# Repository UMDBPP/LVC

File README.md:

# LVC
Low Voltage Cutoff Hardware for LiPo Battery Protection

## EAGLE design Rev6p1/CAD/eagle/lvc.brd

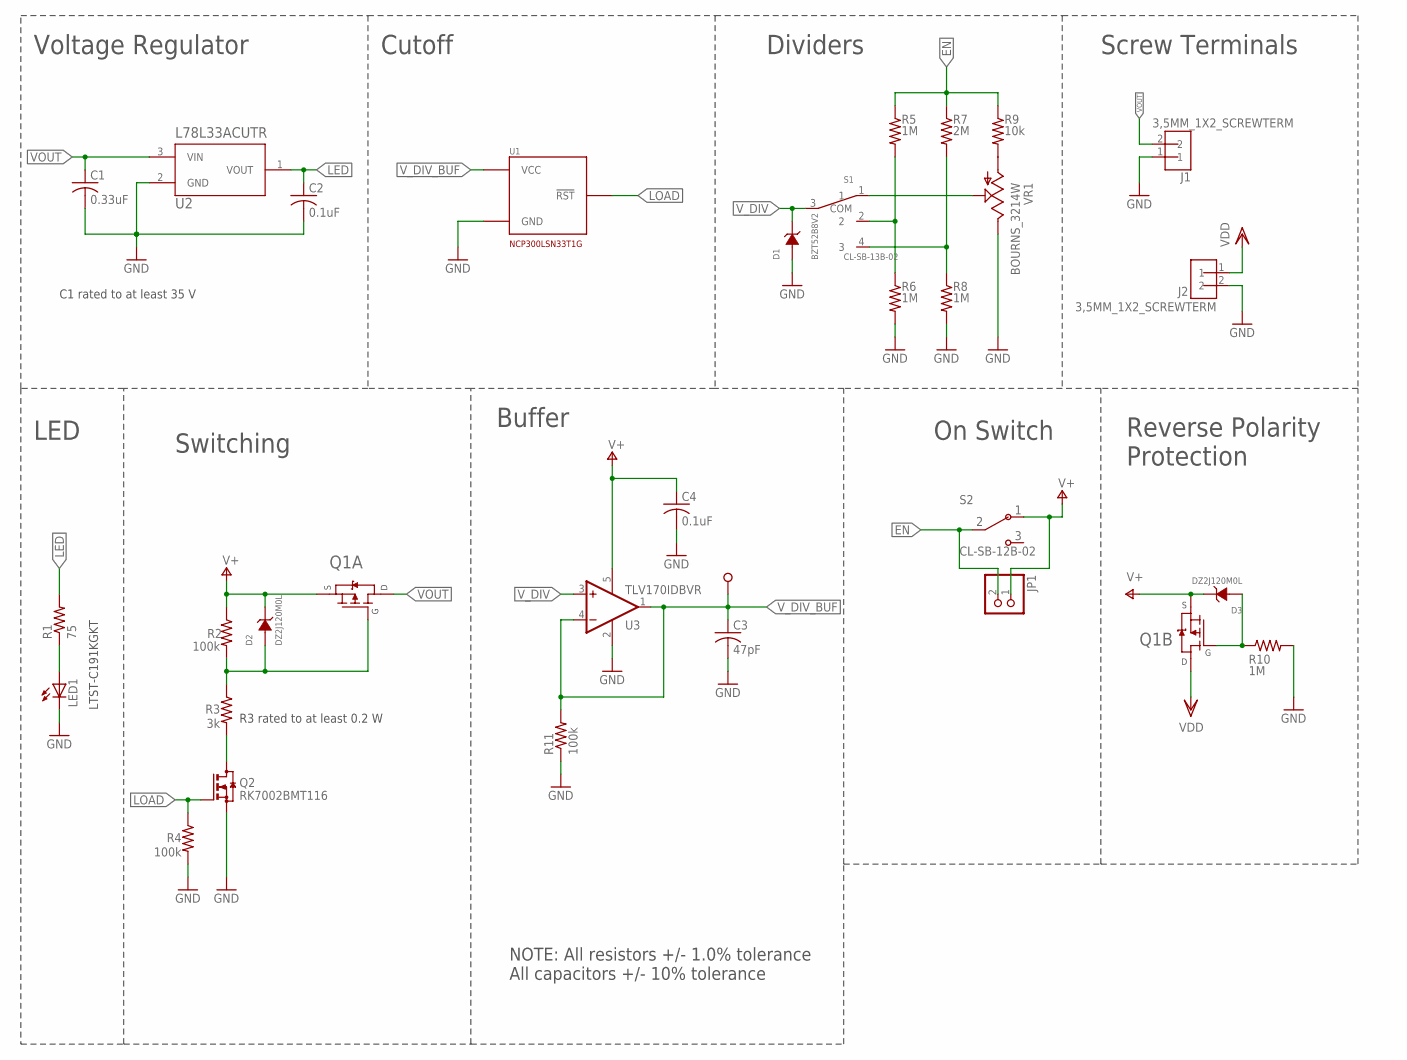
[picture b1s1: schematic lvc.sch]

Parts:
C1: 0.33uF; C0603
C2, C4: 0.1uF; C0603
C3: 47pF; C0603
D1: BZT52B8V2; SOD123
D2, D3: DZ2J120M0L; SMINI2-F5-B
J1, J2: 3,5MM_1X2_SCREWTERM; 3.5MM_1X2
JP1: PINHD-1X2; 1X02
LED1: LEDCHIPLED_0603; CHIPLED_0603
Q1: SI7997DP; POWERPAK-SO-8-DUAL
Q2: RK7002BMT116; SOT23
R1: 75; R0603
R2, R4, R11: 100k; R0603
R3: 3k; R0603
R5, R6, R8, R10: 1M; R0603
R7: 2M; R0603
R9: 10k; R0603
S1: CL-SB-13B-02; CL-SB-13B
S2: CL-SB-12B-02; CL-SB-12B
TP2: TESTPOINTNOCREAM; TP_2.5MM_NOCREAM
U1: NCP300LSN33T1G; SOT23-5
U2: L78L33ACUTR; SOT-89
U3: TLV170IDBVR; SOT23-DBV
VR1: BOURNS_3214W; J-LEAD_TOP_ADJ

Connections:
2_CELL: R5.2, R6.1, S1.2
3_CELL: R7.2, R8.1, S1.4 (3)
EN: JP1.2, R5.1, R7.1, R9.1, S2.1
GND: C1.2, C2.2, C3.2, C4.2, D1.A, J1.1, J2.2, LED1.C, Q2.2 (S), R4.2, R6.2, R8.2, R10.2, R11.1, U1.3 (GND), U2.2 (GND), U3.2 (V-), VR1.3 (E)
LED: C2.1, R1.2, U2.1 (VOUT)
LOAD: Q2.1 (G), R4.1, U1.1 (!RST!)
unnamed: LED1.A, R1.1
unnamed: D2.A, Q1.4 (G), R2.2, R3.1
unnamed: D3.A, Q1.2 (G), R10.1
unnamed: Q2.3 (D), R3.2
unnamed: S1.1, VR1.2 (S)
unnamed: R9.2, VR1.1 (A)
V+: C4.1, D2.C, D3.C, JP1.1, Q1.1 (S), Q1.3 (S), R2.1, S2.2, U3.5 (V+)
VDD: J2.1, Q1.7 (D), Q1.8 (D), Q1.8L (D)
VOUT: C1.1, J1.2, Q1.5 (D), Q1.5L (D), Q1.6 (D), U2.3 (VIN)
V_DIV: D1.C, S1.3 (COM), U3.3 (+IN)
V_DIV_BUF: C3.1, R11.2, TP2.P$1, U1.2 (VCC), U3.1 (OUT), U3.4 (-IN)

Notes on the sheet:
Voltage Regulator
LED
Switching
Dividers
Screw Terminals
On Switch
Reverse Polarity Protection
Cutoff
LTST-C191KGKT
NOTE: All resistors +/- 1.0% tolerance All capacitors +/- 10% tolerance
C1 rated to at least 35 V
R3 rated to at least 0.2 W
Buffer

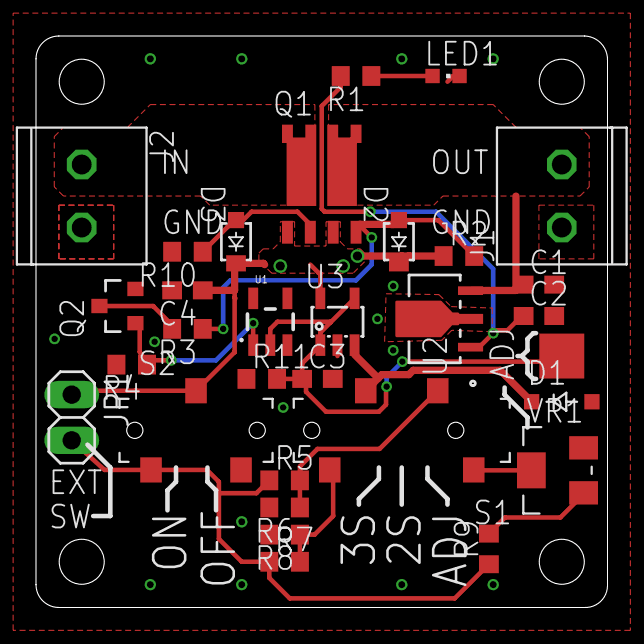
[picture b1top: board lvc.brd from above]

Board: 2 copper layers, 31.8 x 31.8 mm, 31 parts (0 on the bottom side), 17 nets.

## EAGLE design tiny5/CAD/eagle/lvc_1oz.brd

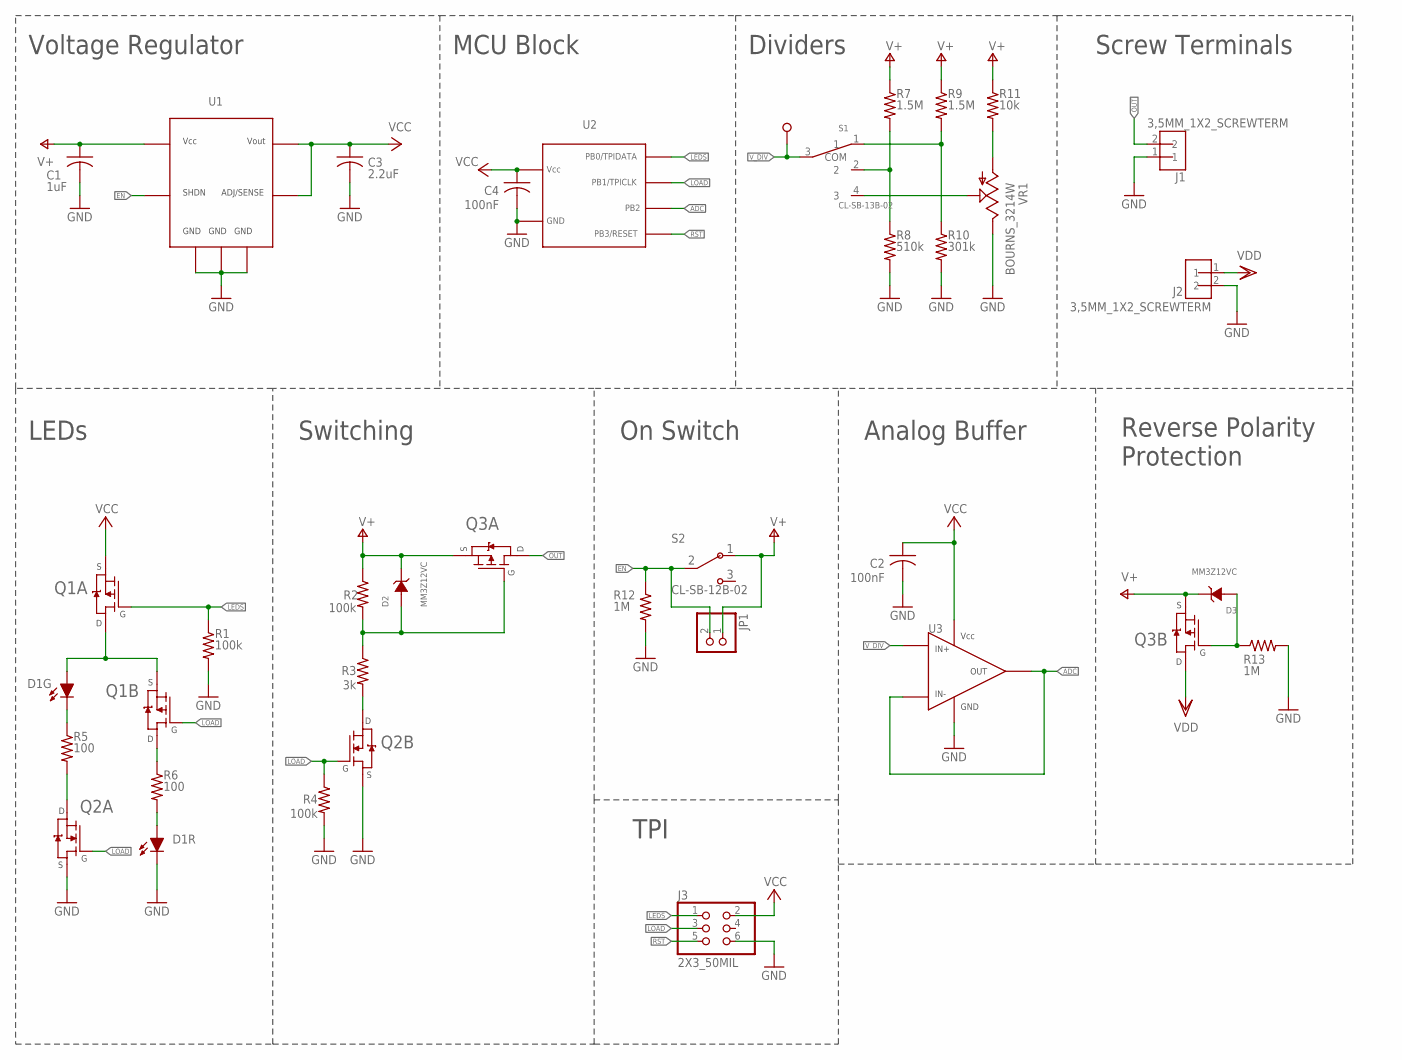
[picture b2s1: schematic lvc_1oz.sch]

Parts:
C1: 1uF; C0603
C2, C4: 100nF; C0603
C3: 2.2uF; C0603
D1: LED-R/G_150141RV73100; 4-PLCC
D2, D3: MM3Z12VC; SOD-323F
J1, J2: 3,5MM_1X2_SCREWTERM; 3.5MM_1X2
J3: 2X3_50MIL; 50MIL_2X3
JP1: PINHD-1X2; 1X02
Q1: FDC6312P; SOT23-6
Q2: PMGD280UN; 6-TSSOP
Q3: SI7997DP; POWERPAK-SO-8-DUAL
R1, R2, R4: 100k; R0603
R3: 3k; R0603
R5, R6: 100; R0603
R7, R9: 1.5M; R0603
R8: 510k; R0603
R10: 301k; R0603
R11: 10k; R0603
R12, R13: 1M; R0603
S1: CL-SB-13B-02; CL-SB-13B
S2: CL-SB-12B-02; CL-SB-12B
TP1: TESTPOINT; TP_2.5MM
U1: LT3007; SOT23-8
U2: ATTINY5; SOT23-6
U3: LT1494; 8-MSOP
VR1: BOURNS_3214W; J-LEAD_TOP_ADJ

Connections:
2_CELL: R7.2, R8.1, S1.2
3_CELL: R9.2, R10.1, S1.1
ADC: U2.4 (PB2), U3.P$2 (IN-), U3.P$6 (OUT)
ADJ: S1.4 (3), VR1.2 (S)
EN: JP1.2, R12.1, S2.1, U1.1 (SHDN)
GND: C1.2, C2.2, C3.2, C4.2, D1.3 (C), J1.1, J2.2, J3.6, Q2.P$1 (S), Q2.P$4 (S), R1.2, R4.2, R8.2, R10.2, R12.2, R13.2, U1.2 (GND1), U1.3 (GND2), U1.4 (GND3), U2.2 (GND), U3.P$4 (GND), VR1.3 (E)
LEDS: J3.1, Q1.1 (G), R1.1, U2.1 (PB0/TPID)
LOAD: J3.3, Q1.3 (G), Q2.P$2 (G), Q2.P$5 (G), R4.1, U2.3 (PB1/TPICLK)
unnamed: D1.4 (C), R5.1
unnamed: Q2.P$6 (D), R5.2
unnamed: D1.2 (A), Q1.2 (S), Q1.6 (D)
unnamed: Q1.4 (D), R6.1
unnamed: D2.1 (A), Q3.4 (G), R2.2, R3.1
unnamed: D3.1 (A), Q3.2 (G), R13.1
unnamed: Q2.P$3 (D), R3.2
unnamed: R11.2, VR1.1 (A)
OUT: J1.2, Q3.5 (D), Q3.5L (D), Q3.6 (D)
RA: D1.1 (A), R6.2
RST: J3.5, U2.6 (PB3/RST)
V+: C1.1, D2.2 (C), D3.2 (C), JP1.1, Q3.1 (S), Q3.3 (S), R2.1, R7.1, R9.1, R11.1, S2.2, U1.5 (VCC)
VCC: C2.1, C3.1, C4.1, J3.2, Q1.5 (S), U1.7 (OUT), U1.8 (ADJ/SENSE), U2.5 (VCC), U3.P$7 (VCC)
VDD: J2.1, Q3.7 (D), Q3.8 (D), Q3.8L (D)
V_DIV: S1.3 (COM), TP1.P$1, U3.P$3 (IN+)

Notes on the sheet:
Voltage Regulator
MCU Block
LEDs
Switching
Dividers
Screw Terminals
Analog Buffer
TPI
On Switch
Reverse Polarity Protection

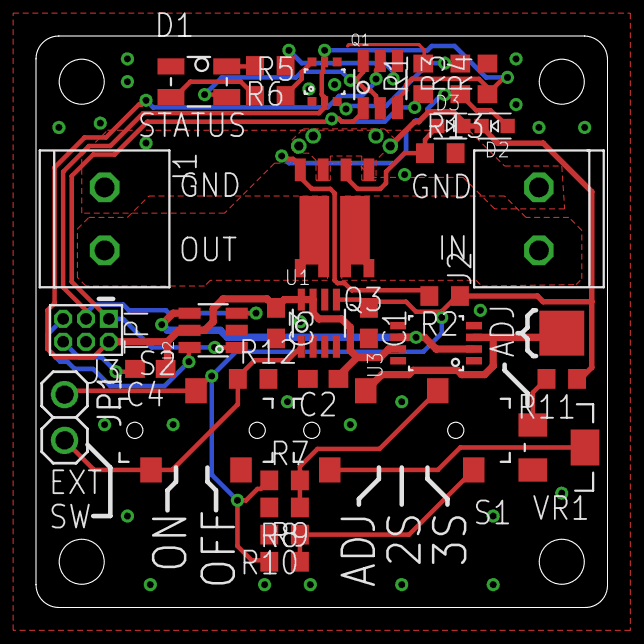
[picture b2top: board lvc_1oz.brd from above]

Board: 2 copper layers, 31.8 x 31.8 mm, 34 parts (0 on the bottom side), 23 nets.

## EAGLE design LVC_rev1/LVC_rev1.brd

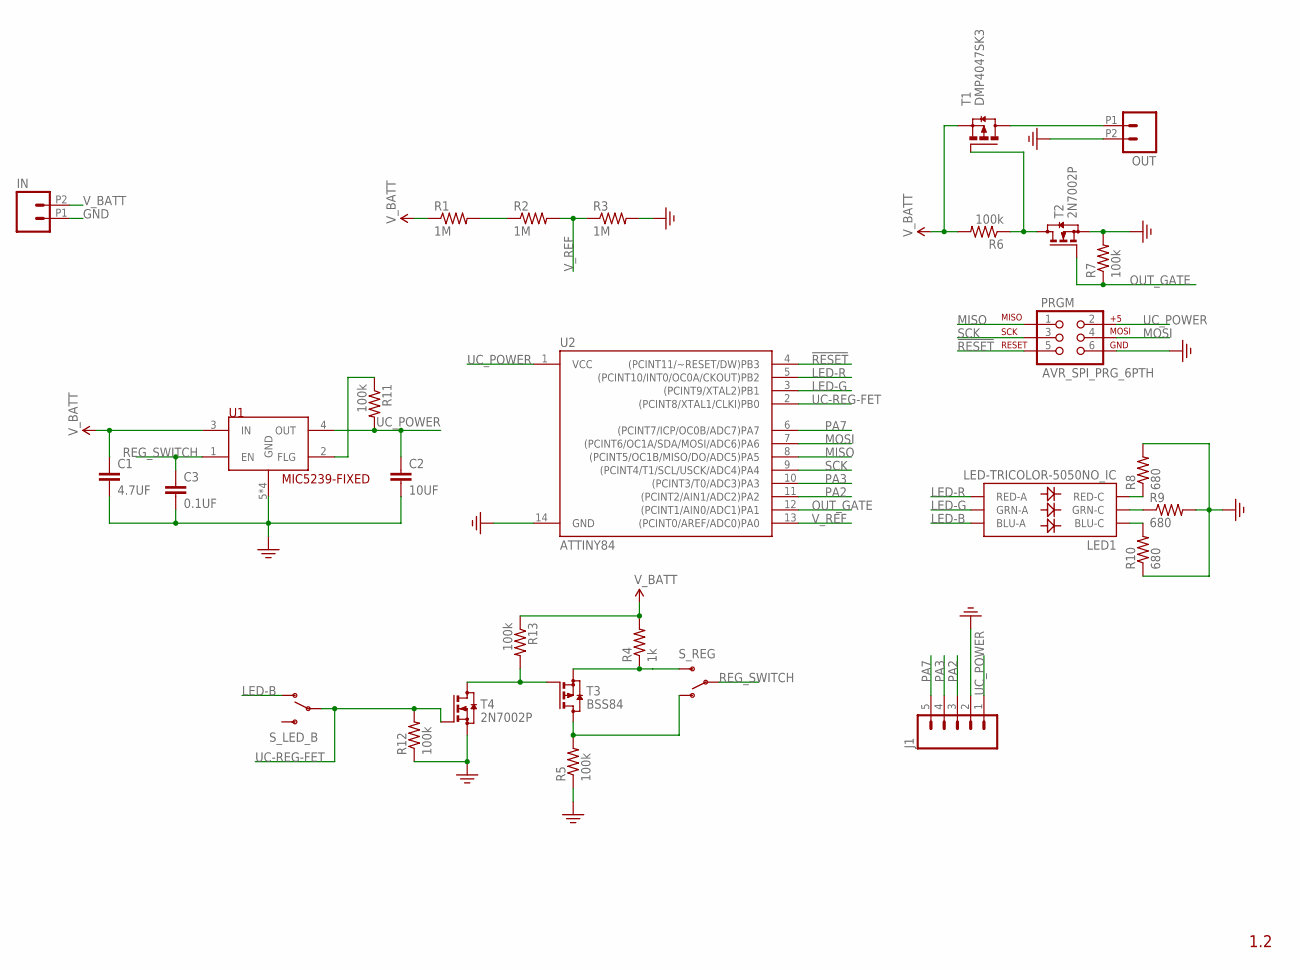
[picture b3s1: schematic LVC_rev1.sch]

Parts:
C1: 4.7UF; C1206
C2: 10UF; C0805
C3: 0.1UF; C0603
IN: M022.54MM_SCREWTERM; 1X02_2.54_SCREWTERM
J1: M05PTH; 1X05
LED1: LED-TRICOLOR-5050NO_IC; LED-TRICOLOR-5050
OUT: M022.54MM_SCREWTERM; 1X02_2.54_SCREWTERM
PRGM: AVR_SPI_PRG_6PTH; 2X3
R1, R2, R3: 1M; R0603
R4: 1k; R0603
R5, R6, R7, R11, R12, R13: 100k; R0603
R8, R9, R10: 680; R0603
S_LED_B: SWITCH-SPDTPTH; SWITCH-SPDT
S_REG: SWITCH-SPDTPTH; SWITCH-SPDT
T1: DMP4047SK3; TO252
T2, T4: 2N7002P; SOT23
T3: BSS84; SOT23
U1: MIC5239-FIXED; SOIC8
U2: ATTINY84; SO14

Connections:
!RESET: PRGM.5, U2.4 ((PCINT11/~RESET/DW)PB3)
BATT_OUT: OUT.P1 (1), T1.3 (D)
GND: C1.2, C2.2, C3.2, IN.P1 (1), J1.2, OUT.P2 (2), PRGM.6, R3.2, R5.1, R7.2, R8.2, R9.2, R10.1, R12.1, T2.2 (S), T4.2 (S), U1.5 (GND), U1.6 (GND), U1.7 (GND), U1.8 (GND), U2.14 (GND)
LED-B: LED1.3 (BLU-A), S_LED_B.1 (O)
LED-G: LED1.1 (GRN-A), U2.3 ((PCINT9/XTAL2)PB1)
LED-R: LED1.2 (RED-A), U2.5 ((PCINT10/INT0/OC0A/CKOUT)PB2)
MISO: PRGM.1, U2.8 ((PCINT5/OC1B/MISO/DO/ADC5)PA5)
MOSI: PRGM.4, U2.7 ((PCINT6/OC1A/SDA/MOSI/ADC6)PA6)
unnamed: LED1.6 (GRN-C), R9.1
unnamed: R4.1, S_REG.3 (S), T3.2 (S)
unnamed: R1.2, R2.1
unnamed: R5.2, S_REG.1 (O), T3.3 (D)
unnamed: R6.1, T1.1 (G), T2.3 (D)
unnamed: LED1.5 (RED-C), R8.1
unnamed: R11.1, U1.2 (FLG)
unnamed: LED1.4 (BLU-C), R10.2
unnamed: R13.2, T3.1 (G), T4.3 (D)
OUT_GATE: R7.1, T2.1 (G), U2.12 ((PCINT1/AIN0/ADC1)PA1)
PA2: J1.3, U2.11 ((PCINT2/AIN1/ADC2)PA2)
PA3: J1.4, U2.10 ((PCINT3/T0/ADC3)PA3)
PA7: J1.5, U2.6 ((PCINT7/ICP/OC0B/ADC7)PA7)
REG_SWITCH: C3.1, S_REG.2, U1.1 (EN)
SCK: PRGM.3, U2.9 ((PCINT4/T1/SCL/USCK/ADC4)PA4)
UC-REG-FET: R12.2, S_LED_B.2, T4.1 (G), U2.2 ((PCINT8/XTAL1/CLKI)PB0)
UC_POWER: C2.1, J1.1, PRGM.2, R11.2, U1.4 (OUT), U2.1 (VCC)
V_BATT: C1.1, IN.P2 (2), R1.1, R4.2, R6.2, R13.1, T1.2 (S), U1.3 (IN)
V_REF: R2.2, R3.1, U2.13 ((PCINT0/AREF/ADC0)PA0)

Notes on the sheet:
1.2

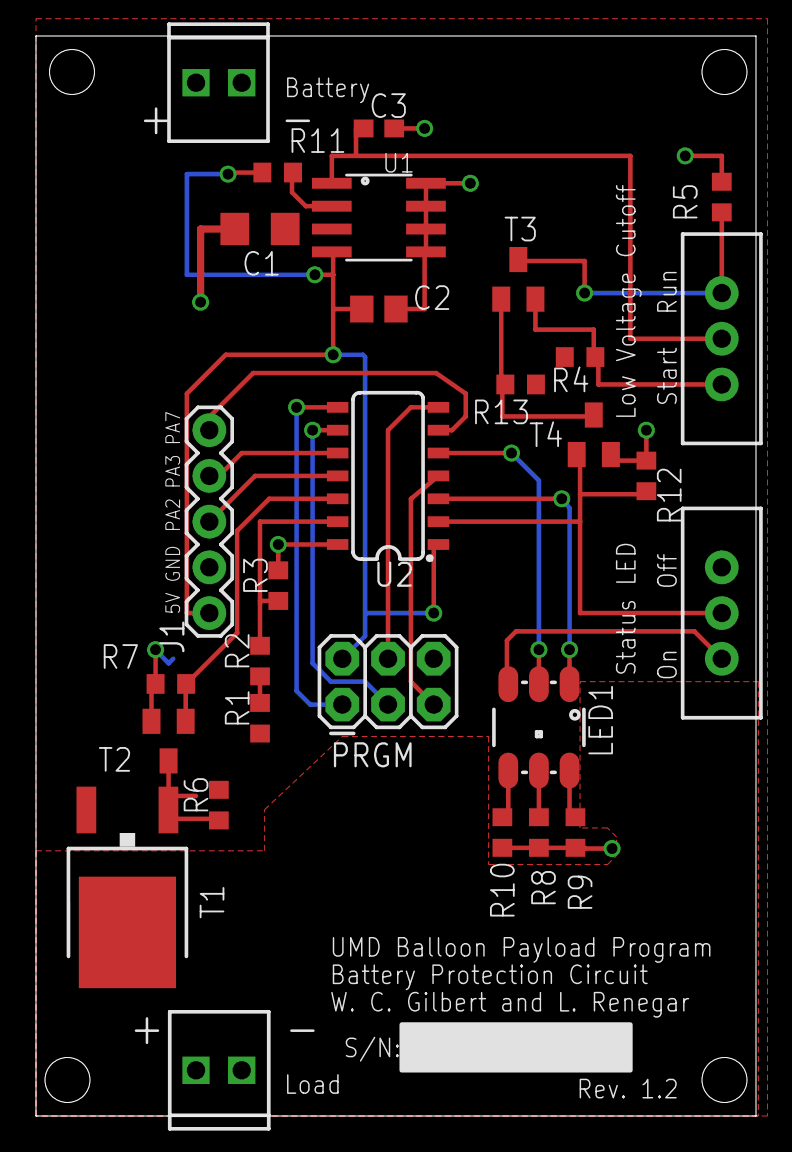
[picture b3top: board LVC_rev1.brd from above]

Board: 2 copper layers, 40.0 x 60.0 mm, 29 parts (0 on the bottom side), 27 nets.

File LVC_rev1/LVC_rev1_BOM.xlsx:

UMD BPP Low Voltage Cutoff Rev 1.2 BOM
Item # | Ref Des | Qty | Manufacturer | Mfg Part # | Description | Package | Type | Dist. 1 | Dist. 1 Part No. | Dist. 2 | Dist. 2 Part No.
1 | C1 | 1 | Samsung EMA | CL31B475KBHNNNE | CAP CER 4.7UF 50V X7R 1206 | 1206 | SMD | Digi-Key | 1276-2789-1-ND
2 | C2 | 1 | Samsung EMA | CL21A106KOQNNNE | CAP CER 10UF 16V X5R 0805 | 0805 | SMD | Digi-Key | 1276-1096-1-ND
3 | C3 | 1 | Murata | GRM188R71E104KA01D | 0.10µF ±10% 25V X7R Ceramic Capacitor | 0603 | SMD | Digi-Key | 490-1524-1-ND
4 | LED1 | 1 | YETDA | 5060BRG4 | LED RGB Common Cathode |  | SMD | Sparkfun | COM-10866
5 | R1, 2, 3 | 3 |  |  | 1M, 0.1% | 0603 | SMD | Digi-Key | A102234CT-ND
6 | R4 | 1 |  |  | 1k, 5% | 0603 | SMD | Digi-Key | 311-1.0KGRCT-ND
7 | R5, 6, 7, 11, 12, 13 | 6 |  |  | 100k, 5% | 0603 | SMD | Digi-Key | 311-100KGRCT-ND
8 | R8, 9, 10 | 3 |  |  | 680, 5% | 0603 | SMD | Digi-Key | 1276-5058-1-ND
9 | U1 | 1 | Micrel | MIC5239-5.0YM | IC REG LDO 5V 0.5A 8SOIC | 8-SOIC | SMD | Digi-Key | 576-1838-5-ND
10 | U2 | 1 | Atmel | ATTINY84-20SSU | IC MCU 8BIT 8KB FLASH 14SOIC | 14-SOIC | SMD | Digi-Key | ATTINY84-20SSU-ND
11 | T1 | 1 | Diodes Incorporated | DMP4047SK3-13 | MOSFET P-CH 40V 20A TO252 | TO-252 | SMD | Digi-Key | DMP4047SK3-13DICT-ND
12 | T2, 4 | 2 | NXP | 2N7002P,215 | MOSFET N-CH 60V 0.36A SOT-23 | SOT23-3 | SMD | Digi-Key | 568-5818-1-ND
13 | T3 | 1 | Infineon | BSS84PH6327XTSA2 | MOSFET P-CH 60V 170MA SOT-23 | SOT23 | SMD | Digi-Key | BSS84PH6327XTSA2CT-ND
14 | S1, 2 | 2 | Sparkfun |  | SPDT Slide Switch |  | Thru-Hole | Sparkfun | COM-09609
15 | PRGM | 1 | Sparkfun | PRT-12807 | 6 Pin programming header |  | Thru-Hole | Sparkfun | PRT-12807
16 | J1 |  |  |  | 5 pin linear header 0.1" spacing |  |  |  | Do not populate
17
18
19
20
21
22

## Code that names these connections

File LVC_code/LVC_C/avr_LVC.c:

// Low Voltage Cutoff Code
// Written by: William Cooper Gilbert on 11 November, 2015
// Revised by: Aravind Ramakrishnan on 23 May, 2016
// Revised by: William Cooper Gilbert on 24 May, 2016
// Rewritten by: Aravind Ramakrishnan on 26 June, 2016 (from Arduino to AVR C)
// Thanks given to Nick Rossomando for guidance

/*
PURPOSE
The purpose of this program is to prevent permanent damage of lithium polymer (LiPo) flight batteries due to deep discharge, where the battery is depleted beyond 80% of its
stated capacity, as indicated by the voltage dropping below 3.25v per cell. This is achieved by using MOSFETs as swtiches, with the gates controlled by an AT-Tiny 84 micro-
controller. When the flight battery in question is above the designated 3.25v per cell voltage, as read by the microcontroller, the gates are set to allow current to flow
to the load, and a green LED is used to show that the battery is above the threshold. When the battery voltage drops below 3.25v per cell, the gates are set to turn off the
current to the load, a red LED is turned on to indicate this visually, and a countdown begun, for ~1.5 hours. If the battery dropped below 3.25v per cell for only a brief time,
the system will turn back on, current will flow to the load, and the green LED will be reactivated. However, it the battery is genuinely depleted, and remains depleted for ~1.5 hours,
the microcontroller will turn off the enable pin that allows the voltage regulator powering the microcontroller to operate, shutting the entire system down except for the
quiescent current flowing through the regulator. This state is called ultra low power mode. A blue LED is used to indicate the status of the enable pin on the regulator: the blue 
LED being on indicates that the regulator is enabled, while the blue LED being off indicates that the regulator is not enabled. A toggle switch on the board allows the blue LED
to be disconnected to save power during flight.

HARDWARE
Surface-mount Device (SMD) Low Voltage Cutoff (LVC) Circuit Board using AT-Tiny 84 microcontroller

OPERATION
Set switches to RUN and LED ON, and connect battery, observe all LEDs are off
Set switch to START, observe blue and green LEDs on simultaneously
Set switch to LED OFF, observe only green LED on
Set switch to RUN, observe only the green LED on
 */

/* Includes */
#include <avr/io.h>
#include <util/delay.h>

/* Pin Definitions */
#define VOLTAGE_DIV PA0 // pin for the voltage divider, used to read the value of the battery. Use in analog mode.
#define LOAD PA1 // pin for Load MOSFETs, used to allow current to flow to the load
#define ENABLE PB0 // digital pin for Enable MOSFETs, used to enable voltage regulator operation
#define GREEN_LED PB1 // digital pin for the Green LED, meaning the battery is charged
#define RED_LED PB2 // digital pin for the Red LED, meaning the battery is depleted

/* Behavioral Constants */
#define LOAD_THRESHOLD 663 // battery threshold with load. 663/1023*5*3: 9.72 volts. *5 becuase this is a 5V microcontroller, *3 becuase this is a 3-cell LiPo (~3.25v per cell threshold). *** From testing, actual cutoff appears to be 9.67V.
#define NO_LOAD_THRESHOLD 700 // battery threshold with no load. 700/1023*5*3: 10.26 volts (Arbitrary, but at least 0.5v greater than Load Threshold voltage). *** From testing, actual value appears to be 10.50V.
#define WAIT_TIME 5000 // time after battery voltage drops below threshold with load before the enable pin is turned off, putting the system into ultra low power mode

/* Function Prototypes */
void init_ADC(); // for setting up the analog conversion on the voltage divider pin
int read_ADC(); // read the voltage divider pin
void work(); // normal execution
void halt(char *battery_status); // battery is now depleted, so turn load off, set LED output
void wait(int *time); // while battery is depleted, increment timer to check for timeout and wait
void resurrect(char *battery_status, int *time); // if battery depletion reading was in error, continue executing normally
void kill(); // after timeout, put into ultra low power mode

int main() {
	/* Program Variables */
	int voltage; // value of current voltage.
	char battery_status = 'a'; // Battery on/off. On = 'a', OFF = 'd'.
	int time = 0; // variable to keep track of runtime after battery drops below threshold.

	/* Enable Pins */
	DDRA |= (1 << LOAD);
	DDRB |= (1 << ENABLE);
	DDRB |= (1 << GREEN_LED);
	DDRB |= (1 << RED_LED);
	init_ADC();

	/* Execution Block */
	while (1) {
		voltage = read_ADC();
		if (battery_status == 'a') { // if battery is ON
			PORTB |= (1 << ENABLE); // set system to "run", the mode used during flight
			if (voltage > LOAD_THRESHOLD) { // if battery is charged
				work();
			}
			else { // if battery is depleted
				halt(&battery_status);
			}
		}
		else {
			if (time < WAIT_TIME) { // if inactivity countdown has not yet expired
				if (voltage < NO_LOAD_THRESHOLD) { // if battery remains depleted
					wait(&time);
				}
				else { // if battery depletion reading was in error
					resurrect(&battery_status, &time);
				}
			}
			else { // if inactivity countdown has expired
				kill();
			}
		}
	}
	return 0; // should never be reached
}

void init_ADC() {
	ADCSRA |= (1 << ADPS2) | (1 << ADPS1) | (0 << ADPS0); // set prescalar to 16
	// ADMUX is fine as it is - PA0 is set with 5:0 set to 0, and to use Vcc, REFS{0,1} should be 0
	DIDR0 |= (1 << ADC0D); // disable digital input
	// For ATTiny84, there is no free running mode
	ADCSRA |= (1 << ADEN); // enable analog digital conversion
}

int read_ADC() {
	ADCSRA |= (1 << ADSC); // start analog digital conversion
	while (ADCSRA & (1 << ADSC)); // wait for read to finish
	return ADC; // return analog value: Vin * 1024 / Vref. (Vref is 5V)
}

void work() {
	PORTA |= (1 << LOAD); // turn load ON
	PORTB |= (1 << GREEN_LED); // turn green LED ON
	PORTB &= ~(1 << RED_LED); // turn red LED OFF
}

void halt(char *battery_status) {
	PORTA &= ~(1 << LOAD); // turn the load OFF
	PORTB &= ~(1 << GREEN_LED); // turn the green LED OFF
	PORTB |= (1 << RED_LED); // turn the red LED ON
	*battery_status = 'd'; // turn battery off
	_delay_ms(3000); // wait three seconds for transients to settle
}

void wait(int *time) {
	(*time)++; // increment inactivity countdown
	_delay_ms(1000); // inactivity countdown is by seconds
}

void resurrect(char *battery_status, int *time) {
	*battery_status = 'a';
	*time = 0;
	_delay_ms(3000); // wait three seconds for transients to settle
}

void kill() {
	PORTB &= ~(1 << ENABLE); // put the battery into ultra low power mode
}

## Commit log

2016-05-21 Rev 1.2 - added C3 to fix start/run switch
2016-05-21 Updated BOM for rev 1.2
2016-05-22 Fixed via error
2016-05-22 Added .gitignore
2016-05-22 Changed documentation error with T2
2016-05-22 Removed extraneous files
2016-05-22 Updated gitignore
2016-05-22 Removed eagle preferences file from git repository (contains data about local machine, not project)
2016-05-27 uploaded the current code for the LVC
2016-05-27 removed vim swap file
2016-05-27 Fixed typo
2016-06-27 rewrote for AVR C, as Arduino is the devil.
2017-05-09 created directory structure for ATTiny5 revision
2017-05-09 created program template, compile script
2017-05-09 initial code commit
2017-05-09 adc initialization
2017-05-09 revision 1 of tiny5 lvc code
2017-05-09 fixed potential error in lvc code
2017-05-09 clock is now set
2017-05-10 revision 2 of lvc code for tiny5
2017-06-27 Added more comments to tiny5 code
2017-07-08 Added resistor.lbr
2017-07-08 mcu lbr
2017-07-09 added voltage reg library
2017-07-09 second LDO added
2017-07-13 Added new choice of LDO
2017-07-14 updated software to reflect design changes
2017-07-14 program fixed to be within 512 bytes
2017-07-14 LDO added to schematic
2017-07-14 added supporting libraries
2017-07-14 added mcu block, updated libraries
2017-07-14 Went from adjustable to fixed voltage reg.
2017-07-22 Added op amp
2017-07-22 Added pin 1 mark to 8-MSOP package
2017-07-22 Added slide switch part
2017-07-22 library updates
2017-07-22 Added 3.5mm screw terminal part.
2017-07-22 Added zener diode.
2017-07-22 SQJ463EP transistor added
2017-07-22 added low-rung shit tier dual n-channel mosfet
2017-07-22 Added low-rung shit tier dual P-Channel MOSFET
2017-07-23 Prettified MOSFET symbols
2017-07-23 Added trimpot.
2017-07-23 Added LED
2017-07-23 added value and name to the package
2017-07-23 Added 50 mil header.
2017-07-23 Started layout
2017-07-23 added 2-pos switch
2017-07-24 Finished routing
2017-07-25 Prettified schematic
2017-10-04 updated schematic for reverse polarity protection
2017-10-05 yet another transistor (P-FET) update
2017-10-06 Routed new transistor. Cleaned up transistor package definition
2017-10-06 updated silkscreen, new renders, created gerbers
2017-10-24 fixed bug in lvc code
2018-03-10 1oz board
2018-03-10 gerbers
2018-03-16 Added Rev4
2018-03-16 Updated voltage divider resistor values
2018-03-19 Added comparator protection; cleaned up schematic
2018-03-26 Added Rev4 final
2018-04-30 Initial pass at Rev6 with buffer
    Buffer required to prevent voltage divider from driving the NFET directly, because evidently a few microamps of bias current is enough to ruin somebody's day.
2018-05-02 Updated buffer to be upstream of comparator
2018-05-07 Updated diode footprints
2018-05-07 Cleaned up Gerbers
2018-05-22 Cleaned up component naming on Rev 1
2018-05-22 Added rev 6.1; moved test point past buffer; cleaned up schematic
    Test point upstream of buffer caused observer effect due to multimeter input impedance
2018-05-23 Updated revision text on board
2025-04-04 2025 LVC revision 0, simpler than previous verisions

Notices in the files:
parts and their libraries:
SparkFun-Connectors: Licensing: Creative Commons ShareAlike 4.0 International - https://creativecommons.org/licenses/by-sa/4.0
